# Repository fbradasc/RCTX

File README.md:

# RCTX - Multi-band R/C System

**Multi-band** because it's designed to work in the following **R/C** frequencies bands:

| Frequency | MHz/GHz | Supported               |
| :-------: | :-----: | :---------------------: |
| 13        |     MHz |                       y |
| 27        |     MHz |                       y |
| 30        |     MHz |                       y |
| 35        |     MHz |                       y |
| 40        |     MHz |                       y |
| 50-55     |     MHz |                       y |
| 70-75     |     MHz |                       y |
| 433       |     MHz |                       y |
| 440       |     MHz |                       y |
| 460       |     MHz |                       y |
| 866       |     MHz | with an external module |
| 900       |     MHz | with an external module |
| 2.4       |     GHz |                       y |

**System** because it's composed by two components:
- the **Encoder** (the remote command)
- the **Decoder** (the receiver)

## Common hardware description
Both components are designed around the Silicon Labs' **EFR32MG12** (_Multi-Protocol Wireless SoC_).

The **EFR32MG12** is equipped with both a _2.4 GHz_ transceiver and a _Sub-GHz_ transceiver tunable as low as _110 MHz_.

To go as low as 13 MHz the Sub-GHz transceiver is configured to work in the _110-350 MHz_ wideband and coupled with the Mini Cicruits' **ADE-1+** (_bidirectional double balanched diode mixer_) with a _LO_ frequency of _110 MHz_, as for the following frequency conversion scheme:
```
 10- 80 -(+110)-> 120-190 band pass
430-460 -(-110)-> 320-350 band pass

    10       80           430     460
     +--...--+             +--...--+
    /         \           /         \        [ Antennas ]
   /           \         /           \
--+             +--...--+             +--

                    ^
                    |
                    v
             110 ->(X)                       [ ADE-1+ ]
                    ^
                    |
                    v
    120     190           320     350
     +--...--+             +--...--+
    /         \           /         \        [ EFR32MG12 Sub-GHz transceiver ]
   /           \         /           \
--+             +--...--+             +--
```

#### Half and full duplex modes
Each **EFR32MG12** transceiver works in ***half duplex*** mode but using both at the same time a ***full duplex*** link between the **Encoder** and the **Decoder** can be established.

For example, the **Encoder** transmits the commands to the **Decoder** via the *Sub-GHz* channel and at the same time the **Decoder** transmits the telemetry to the **Encoder** on the *2.4 GHz* channel:
| Data | direction | Channel |
| :--: | :--: | :--: |
| _Commands_ | Encoder **-->** Decoder | _Sub-GHz_ |
| _Telemetry_ | Encoder **<--** Decoder | _2.4 GHz_ |

#### Utilities

Both components are designed to have the following utilities:
| connector | functionality |
| :-- | :-- |
| micro USB | logs and/or control from the PC |
| SD card | firmware upgrade, logs, configurations and telemetry storage |
| buzzer | acoustic feedback |
| Nokia 5110 display | GUI and data visualization |
| serial-interfaced LED driver (MAX6969 or MAX6971) | optical feedback for digital controls |

These utilities are built around the _Silicon Labs'_ **EFM32HG310** microcontroller which acts as an UART bridge to the SD card, Nokia 5110 display, LEDs and buzzer from the **EFR32MG12** point of view and as a CMSIS-DAP, TTY and MSD (SD Card) USB adapter from the PC point of view.
```
[EFR32MG12] <--(SPI)--> [EFM32HG310] <--(USB)--> [PC]
                             ^
                             |
                           (SPI)
                             |
                             v
             ,----------+----+----+---------.
             ^          |         |         |
             |          |         |         |
             v          v         v         v
         [SD Card]  [BUZZER]  [display]  [LEDs]
```

## Encoder

The **Encoder**'s role is to transform the status of the following controls, switches and buttons into commands to be trasmitted to a **Decoder** or R/C receiver:

| Control               | Count | Type    | Note                   |
| :-------------------- | :---: | :------ | :--------------------- |
| Lever sticks          |     4 | analog  |                        |
| Rotary controls       |    12 | analog  |                        |
| On/Mom/Off Switches   |    32 | analog  | converted from digital |
| Push buttons          |     8 | analog  | converted from digital |
| Push buttons          |     2 | digital |                        |

The commands are then incapsulated in a *protocol* and sent via a transmission channel to:

| Destination               | Channel            |
| :------------------------ | :----------------: |
| a **Decoder**             | Radio or ***TBD*** cable |
| a generic R/C receiver    | Radio              |
| another **Encoder**       | DSC cable          |
| a cable controlled device | I2C or UART cable  |

### ***Encoder*** configuration controls

The **Encoder**'s behaviour is controlled by a couple of DP3T (dual pole 3 pos) slide switches and 3 HEX selectors.

#### ***Encoder***'s output selection DP3T slide switch

This slide switch is used to select where the **Encoder**'s commands are sent:

| slide pos | on DSC cable | via radio | on serial cable |
| :-------: | :----------: | :-------: | :-------------: |
| side 1    | X            |           |                 |
| center    |              |           | X               |
| side 2    |              | X         |                 |

#### Configurable DP3T slide switch - **TBD**

This slide switch behaviour can be configured by the user - **TBD**

#### ***RF BAND SEL*** HEX selector

This HEX selector is used to set the RF band on which the **Encoder** can be tuned for commands transmission and telemetry reception:

| HEX pos | RF band       | MHz | GHz | Sub-GHz transceiver | GHz transceiver |
| :-----: | :------------ | :-: | :-: | :-----------------: | :-------------: |
|    0    | 13.560        |  X  |     |   ON: half-duplex   |       (1)       |
|    1    | 26.815-27.995 |  X  |     |   ON: half duplex   |       (1)       |
|    2    | 29.720-30.350 |  X  |     |   ON: half duplex   |       (1)       |
|    3    | 34.945-36.600 |  X  |     |   ON: half duplex   |       (1)       |
|    4    | 40.510-41.200 |  X  |     |   ON: half duplex   |       (1)       |
|    5    | 49.830-50.980 |  X  |     |   ON: half duplex   |       (1)       |
|    6    | 53.100-54.550 |  X  |     |   ON: half duplex   |       (1)       |
|    7    | 70.140        |  X  |     |   ON: half duplex   |       (1)       |
|    8    | 72.010        |  X  |     |   ON: half duplex   |       (1)       |
|    9    | 75.410        |  X  |     |   ON: half duplex   |       (1)       |
|    A    | 433.250       |  X  |     |   ON: half duplex   |       (1)       |
|    B    | 434.025       |  X  |     |   ON: half duplex   |       (1)       |
|    C    | 439.700       |  X  |     |   ON: half duplex   |       (1)       |
|    D    | 458.500       |  X  |     |   ON: half duplex   |       (1)       |
|    E    | 459.500       |  X  |     |   ON: half duplex   |       (1)       |
|    F    | 2.4           |     |  X  |        OFF          | ON: half duplex |

(1): Can be configured to be **ON: half duplex** for **Decoder**s which send on the 2.4 GHz band the *telemetry* back to the **Encoder**

#### ***RX ID*** and ***RX SUB ID*** HEX selectors

The **Encoder**'s custom trasmission protocol is composed by commands packets which can be addressed to up to 256 recipients.

This means that on a given frequncy, and bound to the **Encoder** at the same time, can be tuned:

- Up to 16 (**RX ID**) **Decoder**s each one with up to 15 (**RX SUB ID**) aditional addressable sub modules
- Up to 256 (**RX ID**:**RX SUB ID**) **Decoder**s with no sub modules

#### Robbe/Futaba F14 radio with RCTX mods

|#|Description|Reference on the picture|
|:-:|:-|:-|
|10|micro push buttons|**1** to **8**, **PL** and **PR**|
|16|*Mom-OFF-Mom* switches|**M1** to **M16**|
|2|*DP3T* slide switches|**SL** and **SR**|
|2|R/C sticks|**LEFT STICK** and **RIGHT STICK**|
|12|rotary controls|**R1** to **R12**|
|1|amperometer|**battery level indicator**|
|36|LEDs|on the side and above the **battery level indicator**|
|1|display|**Nokia 5110 display**|
|1|USB connector|**mini USB**|
|1|DB9 connector|flash programming and debug connections|
|1|DB15 connector|on the bottom side of the radio, expansion port with **UART**, **I2C**, **DSC** and tranceivers' mode connections|
|1|micro SD slot|**Kingston micro SD Card adapter**|
|3|hexadecimal encoders|**RX *ID***, **RX *SUB ID*** and ***RF* BAND SEL**|
|1|power switch|**ON/OFF**|

## Decoder

The **Decoder**'s main role is to produce a stream of signals on the *CRSF (Crossfire) bus* to control the actuators attached to such communication bus.

To achieve this task the **Decoder** merges the data coming from the sensors attached to its I2C bus with the commands trasmitted by the **Encoder** (either via radio or via ***TBD*** cable.

The **Decoder**, if configured, then compresses the sensors data and the signals produced in a format suitable to be stored on the SD card and to be transmitted back to the **Encoder** as ***telemetry*** data.

### Decoder configuration controls

The **Decoder**'s behaviour is controlled by 3 HEX selectors and a DIP switch.

#### ***RX ID*** and ***RX SUB ID*** HEX selectors

These HEX selectors are used to set the **Decoder**'s address.
Only the commands addressed to its own address (**RX ID** and **RX SUB ID** positions) are processed.

#### ***RF BAND SEL*** HEX selector

This HEX selector is used to set the RF band on which the **Decoder** can be tuned for commands reception and telemetry transmission:

| HEX pos | RF band       | MHz | GHz | Sub-GHz transceiver | GHz transceiver |
| :-----: | :------------ | :-: | :-: | :-----------------: | :-------------: |
|    0    | 13.560        |  X  |     |   ON: half-duplex   |       (1)       |
|    1    | 26.815-27.995 |  X  |     |   ON: half duplex   |       (1)       |
|    2    | 29.720-30.350 |  X  |     |   ON: half duplex   |       (1)       |
|    3    | 34.945-36.600 |  X  |     |   ON: half duplex   |       (1)       |
|    4    | 40.510-41.200 |  X  |     |   ON: half duplex   |       (1)       |
|    5    | 49.830-50.980 |  X  |     |   ON: half duplex   |       (1)       |
|    6    | 53.100-54.550 |  X  |     |   ON: half duplex   |       (1)       |
|    7    | 70.140        |  X  |     |   ON: half duplex   |       (1)       |
|    8    | 72.010        |  X  |     |   ON: half duplex   |       (1)       |
|    9    | 75.410        |  X  |     |   ON: half duplex   |       (1)       |
|    A    | 433.250       |  X  |     |   ON: half duplex   |       (1)       |
|    B    | 434.025       |  X  |     |   ON: half duplex   |       (1)       |
|    C    | 439.700       |  X  |     |   ON: half duplex   |       (1)       |
|    D    | 458.500       |  X  |     |   ON: half duplex   |       (1)       |
|    E    | 459.500       |  X  |     |   ON: half duplex   |       (1)       |
|    F    | 2.4           |     |  X  |        OFF          | ON: half duplex |

(1): Can be configured to be **ON: half duplex** for **Decoder**s which send on the 2.4 GHz band the *telemetry* back to the **Encoder**.

#### ***RX RADIO EN*** DIP switch

This DIP switch is used to set the ***Decoder***'s source for incoming commands:

- **RX RADIO EN** in position ***1*** *(open)*

    The **Decoder** listens for commands signal on the **DSC_BUS** bus:
    - Turns OFF the radio transceiver.
    - Commands signal can only be received from the ***DSC_BUS***.
    - Telemetry data can only be send to the ***DSC_BUS***.

- **RX RADIO EN** in position ***2*** *(closed)*

    The **Decoder** listens for commands coming from the radio:
    - Turns ON the radio tranceivers.
    - Commands signal can only be received from the radio transceiver.
    - Commands signal received from the radio transceiver is mirrored, as is, over the ***DSC_BUS***.
    - Telemetry data can only be send to the radio transceiver.
    - Telemetry data received from the ***DSC_BUS*** is fused with the local telemetry data before it's sent to the radio transceiver.

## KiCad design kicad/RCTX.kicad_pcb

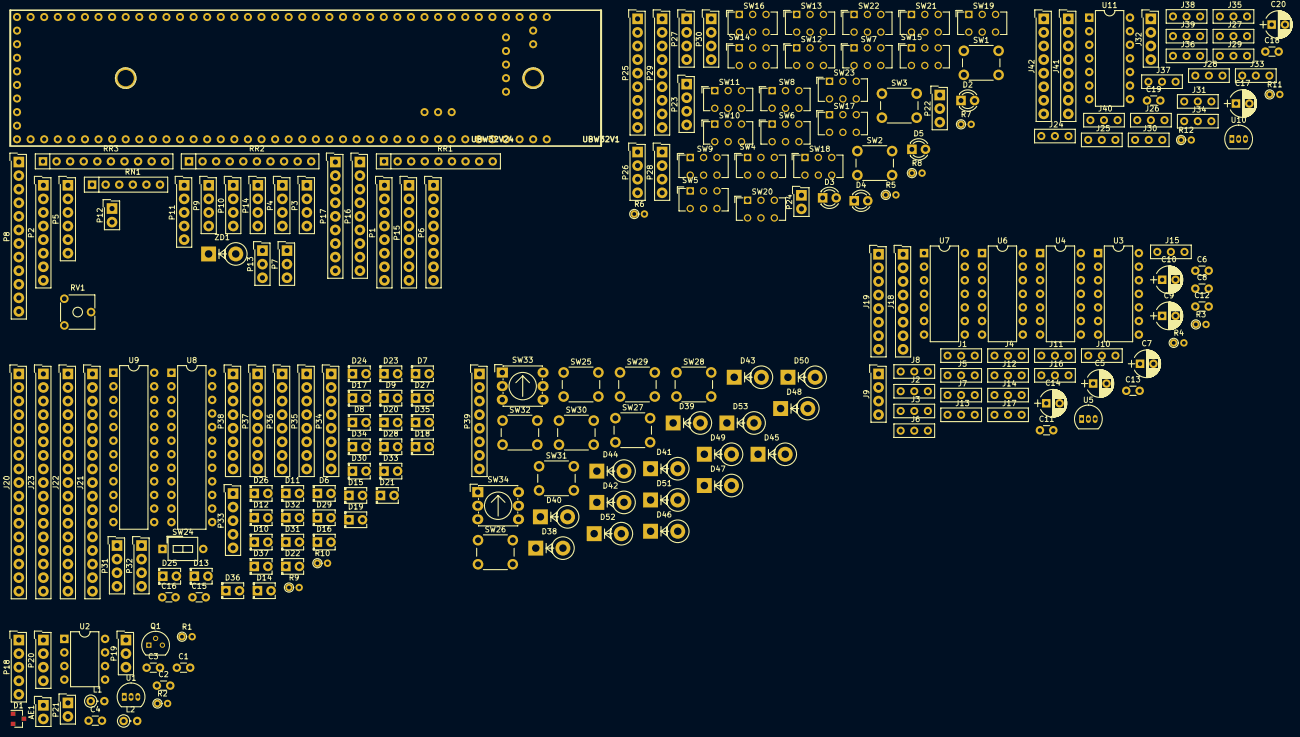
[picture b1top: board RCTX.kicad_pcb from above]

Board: 2 copper layers, 222 parts (0 on the bottom side), 305 nets, no tracks yet.

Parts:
AE1: Antenna_Shield; SL-102-X-XX_1x02
C1, C12, C18: 100nF; C_Disc_D3.0mm_W1.6mm_P2.50mm
C2, C3: 10nF; C_Disc_D3.0mm_W1.6mm_P2.50mm
C4: 1nF; C_Disc_D3.0mm_W1.6mm_P2.50mm
C5, C9, C10, C14: 100uF; CP_Radial_D5.0mm_P2.50mm
C6, C8, C11, C13: 1uF; C_Disc_D3.0mm_W1.6mm_P2.50mm
C7, C17: 1uF; CP_Radial_D5.0mm_P2.50mm
C15, C16: 0.1uF; C_Disc_D3.0mm_W1.6mm_P2.50mm
C19: C; C_Disc_D3.0mm_W1.6mm_P2.50mm
C20: CP; CP_Radial_D5.0mm_P2.50mm
D1: BAV99; SOT-23
D2: RED; LED_D3.0mm
D3: WHITE; LED_D3.0mm
D4: GREEN; LED_D3.0mm
D5: BLUE; LED_D3.0mm
D6, D7, D8, D9, D10, D11, D12, D13, D14, D15, D16, D17, D18, D19, D20, D21, D22, D23, D24, D25, D26, D27, D28, D29, D30, D31, D32, D33, D34, D35, D36, D37: LED; LED_D2.0mm_W4.0mm_H2.8mm_FlatTop
D38, D39, D40, D41, D42, D43, D44, D45, D46, D47, D48, D49, D50, D51, D52, D53: 1N4148; D_5W_P5.08mm_Vertical_KathodeUp
J1, J24: ROTARY_4; SRV_1
J2, J25: ROTARY_5; SRV_1
J3, J26: ROTARY_3; SRV_1
J4, J27: ROTARY_6; SRV_1
J5, J28: ROTARY_2; SRV_1
J6, J29: ROTARY_7; SRV_1
J7, J30: ROTARY_1; SRV_1
J8, J31: ROTARY_8; SRV_1
J9, J32: PWR_BUS; SL-104-X-XX_1x04
J10, J33: H_RIGHT_JOYSTIC; SRV_1
J11, J34: ROTARY_9; SRV_1
J12, J35: V_RIGHT_JOYSTIC; SRV_1
J13, J36: ROTARY_10; SRV_1
J14, J37: H_LEFT_JOYSTIC; SRV_1
J15, J38: ROTARY_11; SRV_1
J16, J39: V_LEFT_JOYSTIC; SRV_1
J17, J40: ROTARY_12; SRV_1
J18, J41: MULTI_PROP_1; SL-108-X-XX_1x08
J19, J42: MULTI_PROP_2; SL-108-X-XX_1x08
J20, J21, J22, J23: Conn_01x17; SL-117-X-XX_1x17
L1: Pickup coil; L_Axial_L5.3mm_D2.2mm_P2.54mm_Vertical_Vishay_IM-1
L2: 10uH; L_Axial_L5.3mm_D2.2mm_P2.54mm_Vertical_Vishay_IM-1
P1: MULTI_PROP_1; SL-108-X-XX_1x08
P2: MULTI_PROP_2; SL-108-X-XX_1x08
P3: SD_CARD; SL-104-X-XX_1x04
P4, P32: LEDs; SL-104-X-XX_1x04
P5: DISPLAY; SL-106-X-XX_1x06
P6: EJTAG + IO_PORT; SL-108-X-XX_1x08
P7, P19: TX_MOD; SL-103-X-XX_1x03
P8: AUX_DB15_PORT; SL-112-X-XX_1x12
P9, P20, P23, P26, P28, P30, P31: PWR_BUS; SL-104-X-XX_1x04
P10: POWER_IN; SL-104-X-XX_1x04
P11: USB; SL-105-X-XX_1x05
P12: BUZZ; SL-102-X-XX_1x02
P13, P22: SW; SL-103-X-XX_1x03
P14, P27: LEDS; SL-104-X-XX_1x04
P15: KEYPAD; SL-108-X-XX_1x08
P16, P25: MULTI_DIGITAL_1; SL-109-X-XX_1x09
P17, P29: MULTI_DIGITAL_2; SL-109-X-XX_1x09
P18: RF MODULE; SL-105-X-XX_1x05
P21, P24: TX_VCC; SL-102-X-XX_1x02
P33: DISPLAY; SL-105-X-XX_1x05
P34, P35, P37, P38: CONN_8; SL-108-X-XX_1x08
P36: Nokia 5110 Display; SL-108-X-XX_1x08
P39: KEYBOARD; SL-108-X-XX_1x08
Q1: BC547; TO-92_Molded_Narrow
R1: 2k2; R_Axial_DIN0204_L3.6mm_D1.6mm_P1.90mm_Vertical
R2: 15k; R_Axial_DIN0204_L3.6mm_D1.6mm_P1.90mm_Vertical
R3, R11: 470; R_Axial_DIN0204_L3.6mm_D1.6mm_P1.90mm_Vertical
R4, R12: 150; R_Axial_DIN0204_L3.6mm_D1.6mm_P1.90mm_Vertical
R5, R6, R7, R8: 330; R_Axial_DIN0204_L3.6mm_D1.6mm_P1.90mm_Vertical
R9, R10: R; R_Axial_DIN0204_L3.6mm_D1.6mm_P1.90mm_Vertical
RN1: 15k; R_Array_SIP6
RR1: 15k; R_Array_SIP9
RR2, RR3: 15K; R_Array_SIP10
RV1: POT; Potentiometer_Trimmer_ACP_CA6v_Horizontal
SW1: Reset; SW_PUSH_6mm_h5mm
SW2: Program; SW_PUSH_6mm_h5mm
SW3: User; SW_PUSH_6mm_h5mm
SW4: RF_SWITCH_3P2V; SW_CuK_JS202011AQN_DPDT_Angled
SW5: LEFT_3P2V; SW_CuK_JS202011AQN_DPDT_Angled
SW6, SW7, SW8, SW9, SW10, SW11, SW12, SW13: LEFT_3P1V; SW_CuK_JS202011CQN_DPDT_Straight
SW14: RIGHT_3P2V_B; SW_CuK_JS202011AQN_DPDT_Angled
SW15: RIGHT_3P2V_A; SW_CuK_JS202011AQN_DPDT_Angled
SW16, SW17, SW18, SW19, SW20, SW21, SW22, SW23: RIGHT_3P1V; SW_CuK_JS202011CQN_DPDT_Straight
SW24: LED_SWITCH; SW_DIP_x1_W7.62mm_Slide_LowProfile
SW25, SW26, SW27, SW28, SW29, SW30, SW31, SW32: SPST; SW_PUSH_6mm_h5mm
SW33, SW34: CODING_SWITCH; Nidec_Copal_SH-7010C
U1: LM78L05_TO92; TO-92_Inline_Narrow_Oval
U2: MB504L; DIP-8_W7.62mm
U3, U4, U6, U7, U11: LM324; DIP-14_W7.62mm
U5, U10: LM117_TO3; TO-92_Inline_Narrow_Oval
U8, U9: MAX6969; DIP-24_W7.62mm
UBW32V1: UBW32V24; UBW32_V24
ZD1: ZENER; D_5W_P5.08mm_Vertical_KathodeUp

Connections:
+3V3: AE1.2, C1.1, C2.2, C3.2, C5.2, C6.1, C7.2, C8.1, C9.2, C10.2, C11.1, C12.1, C12.2, C13.1, C14.2, C17.2, C18.1, C18.2, C19.1, C20.2, J1.1, J2.1, J3.1, J4.1, J5.1, J6.1, J7.1, J8.1, J9.1, J9.3, J10.1, J10.3, J11.1, J12.1, J12.3, J13.1, J14.1, J14.3, J15.1, J16.1, J16.3, J17.1, J24.1, J25.1, J26.1, J27.1, J28.1, J29.1, J30.1, J31.1, J32.1, J32.3, J33.1, J33.3, J34.1, J35.1, J35.3, J36.1, J37.1, J37.3, J38.1, J39.1, J39.3, J40.1, L2.1, P9.1, P9.3, P18.2, P20.1, P20.3, P23.3, P26.1, P26.3, P28.1, P30.1, P30.3, P31.1, P31.3, P34.1, P34.7, P35.1, P35.7, P36.1, P36.2, Q1.3, R1.2, R4.1, R5.2, R6.2, R7.2, R8.2, R12.1, RN1.1, RR1.1, SW1.1, SW2.1, SW3.1, SW5.1, SW5.4, SW6.1, SW6.3, SW7.1, SW7.3, SW8.1, SW8.3, SW9.1, SW9.3, SW10.1, SW10.3, SW11.1, SW11.3, SW12.1, SW12.3, SW13.1, SW13.3, SW15.1, SW15.4, SW16.1, SW16.3, SW17.1, SW17.3, SW18.1, SW18.3, SW19.1, SW19.3, SW20.1, SW20.3, SW21.1, SW21.3, SW22.1, SW22.3, SW23.1, SW23.3, SW24.1, U1.2, U2.4, U3.11, U4.11, U5.2, U6.11, U7.11, U10.2, U11.11, UBW32V1.1, UBW32V1.3, UBW32V1.86
+5V: C1.2, C2.1, C5.1, C6.2, C8.2, C9.1, C10.1, C11.2, C13.2, C14.1, C19.2, C20.1, J9.2, J32.2, P9.2, U1.1, U2.2, U2.3, U2.6, U3.4, U4.4, U6.4, U7.4, U11.4, UBW32V1.2
unnamed: AE1.1, P18.1
unnamed: C3.1, P18.4, P21.2, U1.3
unnamed: C4.1, Q1.2
unnamed: C4.2, R1.1
unnamed: C7.1, J1.3, J2.3, J3.3, J4.3, J5.3, J6.3, J7.3, J8.3, J11.3, J13.3, J15.3, J17.3, R3.1, U5.3
unnamed: C15.1, P37.1, R9.1, U8.1
unnamed: C15.2, P37.7, U8.24
unnamed: C16.1, P38.1, R10.1, U9.1
unnamed: C16.2, P38.7, U9.24
unnamed: C17.1, J24.3, J25.3, J26.3, J27.3, J28.3, J29.3, J30.3, J31.3, J34.3, J36.3, J38.3, J40.3, R11.1, U10.3
unnamed: D1.1, D1.2, L1.1, U2.1
unnamed: D1.3, L1.2, U2.8
unnamed: D2.1, R5.1
unnamed: D2.2, P27.1
unnamed: D3.1, R6.1
unnamed: D3.2, P27.2
unnamed: D4.1, R7.1
unnamed: D4.2, P27.3
unnamed: D5.1, R8.1
unnamed: D5.2, P27.4
unnamed: D6.2, J22.2
unnamed: D7.2, J23.2
unnamed: D8.2, J22.3
unnamed: D9.2, J23.3
unnamed: D6.1, D8.1, D10.1, D12.1, D14.1, D16.1, D18.1, D20.1, D22.1, D24.1, D26.1, D28.1, D30.1, D32.1, D34.1, D36.1, J22.1
unnamed: D10.2, J22.4
unnamed: D7.1, D9.1, D11.1, D13.1, D15.1, D17.1, D19.1, D21.1, D23.1, D25.1, D27.1, D29.1, D31.1, D33.1, D35.1, D37.1, J23.1
unnamed: D11.2, J23.4
unnamed: D12.2, J22.5
unnamed: D13.2, J23.5
unnamed: D14.2, J22.6
unnamed: D15.2, J23.6
unnamed: D16.2, J22.7
unnamed: D17.2, J23.7
unnamed: D18.2, J22.8
unnamed: D19.2, J23.8
unnamed: D20.2, J22.9
unnamed: D21.2, J23.9
unnamed: D22.2, J22.10
unnamed: D23.2, J23.10
unnamed: D24.2, J22.11
unnamed: D25.2, J23.11
unnamed: D26.2, J22.12
unnamed: D27.2, J23.12
unnamed: D28.2, J22.13
unnamed: D29.2, J23.13
unnamed: D30.2, J22.14
unnamed: D31.2, J23.14
unnamed: D32.2, J22.15
unnamed: D33.2, J23.15
unnamed: D34.2, J22.16
unnamed: D35.2, J23.16
unnamed: D36.2, J22.17
unnamed: D37.2, J23.17
unnamed: D38.1, D42.1, D46.1, D50.1, P39.5
unnamed: D38.2, SW25.1
unnamed: D39.1, D43.1, D47.1, D51.1, P39.6
unnamed: D39.2, SW26.1
unnamed: D40.1, D44.1, D48.1, D52.1, P39.7
unnamed: D40.2, SW27.1
unnamed: D41.1, D45.1, D49.1, D53.1, P39.8
unnamed: D41.2, SW28.1
unnamed: D42.2, SW29.1
unnamed: D43.2, SW30.1
unnamed: D44.2, SW31.1
unnamed: D45.2, SW32.1
unnamed: D47.2, SW33.4
unnamed: D49.2, SW33.2
unnamed: D51.2, SW34.4
unnamed: D53.2, SW34.2
unnamed: J1.2, U3.3
unnamed: J2.2, U3.5
unnamed: J3.2, U3.10
unnamed: J4.2, U3.12
unnamed: J5.2, U4.3
unnamed: J6.2, U4.5
unnamed: J7.2, U4.10
unnamed: J8.2, U4.12
unnamed: J10.2, U6.3
unnamed: J11.2, U6.5
unnamed: J12.2, U6.10
unnamed: J13.2, U6.12
unnamed: J14.2, U7.3
unnamed: J15.2, U7.5
unnamed: J16.2, U7.10
unnamed: J17.2, U7.12
unnamed: J18.1, U7.8, U7.9
unnamed: J18.2, U7.1, U7.2
unnamed: J18.3, U6.8, U6.9
unnamed: J18.4, U6.1, U6.2
unnamed: J18.5, U4.8, U4.9
unnamed: J18.6, U4.1, U4.2
unnamed: J18.7, U3.8, U3.9
unnamed: J18.8, U3.1, U3.2
unnamed: J19.1, U3.6, U3.7
unnamed: J19.2, U3.13, U3.14
unnamed: J19.3, U4.6, U4.7
unnamed: J19.4, U4.13, U4.14
unnamed: J19.5, U6.6, U6.7
unnamed: J19.6, U6.13, U6.14
unnamed: J19.7, U7.6, U7.7
unnamed: J19.8, U7.13, U7.14
unnamed: J20.1, P37.8
unnamed: J20.2, U8.5
unnamed: J20.3, U8.6
unnamed: J20.4, U8.7
unnamed: J20.5, U8.8
unnamed: J20.6, U8.9
unnamed: J20.7, U8.10
unnamed: J20.8, U8.11
unnamed: J20.9, U8.12
unnamed: J20.10, U8.13
unnamed: J20.11, U8.14
unnamed: J20.12, U8.15
unnamed: J20.13, U8.16
unnamed: J20.14, U8.17
unnamed: J20.15, U8.18
unnamed: J20.16, U8.19
unnamed: J20.17, U8.20
unnamed: J21.1, P38.8
unnamed: J21.2, U9.5
unnamed: J21.3, U9.6
unnamed: J21.4, U9.7
unnamed: J21.5, U9.8
unnamed: J21.6, U9.9
unnamed: J21.7, U9.10
unnamed: J21.8, U9.11
unnamed: J21.9, U9.12
unnamed: J21.10, U9.13
unnamed: J21.11, U9.14
unnamed: J21.12, U9.15
unnamed: J21.13, U9.16
unnamed: J21.14, U9.17
unnamed: J21.15, U9.18
unnamed: J21.16, U9.19
unnamed: J21.17, U9.20
unnamed: J24.2, J41.8
unnamed: J25.2, J42.1
unnamed: J26.2, J41.7
unnamed: J27.2, J42.2
unnamed: J28.2, J41.6
unnamed: J29.2, J42.3
unnamed: J30.2, J41.5
unnamed: J31.2, J42.4
unnamed: J33.2, U11.3
unnamed: J34.2, J42.5
unnamed: J35.2, U11.5
unnamed: J36.2, J42.6
unnamed: J37.2, U11.10
unnamed: J38.2, J42.7
unnamed: J39.2, U11.12
unnamed: J40.2, J42.8
unnamed: J41.1, U11.13, U11.14
unnamed: J41.2, U11.8, U11.9
unnamed: J41.3, U11.6, U11.7
unnamed: J41.4, U11.1, U11.2
unnamed: L2.2, R2.1
unnamed: P1.1, UBW32V1.45
unnamed: P1.2, UBW32V1.44
unnamed: P1.3, UBW32V1.43
unnamed: P1.4, UBW32V1.42
unnamed: P1.5, UBW32V1.41
unnamed: P1.6, UBW32V1.31
unnamed: P1.7, UBW32V1.30
unnamed: P1.8, UBW32V1.29
unnamed: P2.1, UBW32V1.26
unnamed: P2.2, UBW32V1.25
unnamed: P2.3, UBW32V1.24
unnamed: P2.4, UBW32V1.23
unnamed: P2.5, UBW32V1.19
unnamed: P2.6, UBW32V1.18
unnamed: P2.7, UBW32V1.17
unnamed: P2.8, UBW32V1.16
unnamed: P3.1, P5.5, UBW32V1.39
unnamed: P3.2, P4.2, P5.4, UBW32V1.37
unnamed: P3.3, P5.3, UBW32V1.38
unnamed: P3.4, UBW32V1.33
unnamed: P4.1, UBW32V1.40
unnamed: P4.3, UBW32V1.32
unnamed: P4.4, UBW32V1.78
unnamed: P5.1, UBW32V1.28
unnamed: P5.2, UBW32V1.27
unnamed: P6.1, UBW32V1.36
unnamed: P6.2, UBW32V1.34
unnamed: P6.3, UBW32V1.22
unnamed: P6.4, UBW32V1.7
unnamed: P6.5, UBW32V1.6
unnamed: P6.6, P8.1, RN1.5, UBW32V1.9
unnamed: P6.7, P7.3, P8.2, RN1.4, UBW32V1.8
unnamed: P6.8, P7.2, RN1.6, UBW32V1.35
unnamed: P7.1, UBW32V1.49, UBW32V1.79
unnamed: P8.3, UBW32V1.21
unnamed: P8.4, UBW32V1.20
unnamed: P8.5, UBW32V1.15
unnamed: P8.6, UBW32V1.14
unnamed: P8.7, UBW32V1.13
unnamed: P8.8, UBW32V1.12
unnamed: P8.9, UBW32V1.11
unnamed: P8.10, UBW32V1.10
unnamed: P8.11, RN1.3, UBW32V1.5
unnamed: P8.12, RN1.2, UBW32V1.4
unnamed: P9.4, P10.1, RV1.1, UBW32V1.90
unnamed: P10.2, P10.3, UBW32V1.89
unnamed: P10.4, ZD1.2
unnamed: P11.1, UBW32V1.91
unnamed: P11.2, UBW32V1.92
unnamed: P11.3, UBW32V1.93
unnamed: P11.4, UBW32V1.94
unnamed: P11.5, UBW32V1.95
unnamed: P12.1, UBW32V1.81
unnamed: P12.2, UBW32V1.46
unnamed: P13.1, UBW32V1.48
unnamed: P13.2, UBW32V1.52
unnamed: P13.3, UBW32V1.53
unnamed: P14.1, UBW32V1.57
unnamed: P14.2, UBW32V1.58
unnamed: P14.3, UBW32V1.62
unnamed: P14.4, UBW32V1.63
unnamed: P15.1, RR1.2, UBW32V1.50
unnamed: P15.2, RR1.3, UBW32V1.51
unnamed: P15.3, RR1.4, UBW32V1.54
unnamed: P15.4, RR1.5, UBW32V1.55
unnamed: P15.5, RR1.6, UBW32V1.56
unnamed: P15.6, RR1.7, UBW32V1.59
unnamed: P15.7, RR1.8, UBW32V1.60
unnamed: P15.8, RR1.9, UBW32V1.61
unnamed: P16.1, RR2.2, UBW32V1.64
unnamed: P16.2, RR2.3, UBW32V1.65
unnamed: P16.3, RR2.4, UBW32V1.66
unnamed: P16.4, RR2.5, UBW32V1.67
unnamed: P16.5, RR2.6, UBW32V1.68
unnamed: P16.6, RR2.7, UBW32V1.69
unnamed: P16.7, RR2.8, UBW32V1.70
unnamed: P16.8, RR2.9, UBW32V1.71
unnamed: P16.9, RR2.10, UBW32V1.72
unnamed: P17.1, RR3.2, UBW32V1.73
unnamed: P17.2, RR3.3, UBW32V1.74
unnamed: P17.3, RR3.4, UBW32V1.75
unnamed: P17.4, RR3.5, UBW32V1.76
unnamed: P17.5, RR3.6, UBW32V1.77
unnamed: P17.6, RR3.7, UBW32V1.80
unnamed: P17.7, RR3.8, UBW32V1.82
unnamed: P17.8, RR3.9, UBW32V1.83
unnamed: P17.9, RR3.10, UBW32V1.84
unnamed: P18.3, P19.2
unnamed: P18.5, P19.3
unnamed: P19.1, Q1.1, R2.2
unnamed: P20.4, P21.1
unnamed: P22.1, SW1.2
unnamed: P22.2, SW2.2
unnamed: P22.3, SW3.2
unnamed: P24.1, SW4.3
unnamed: P24.2, SW4.1
unnamed: P25.1, SW5.3
unnamed: P25.2, SW6.2
unnamed: P25.3, SW7.2
unnamed: P25.4, SW8.2
unnamed: P25.5, SW9.2
unnamed: P25.6, SW10.2
unnamed: P25.7, SW11.2
unnamed: P25.8, SW12.2
unnamed: P25.9, SW13.2
unnamed: P29.1, SW15.3
unnamed: P29.2, SW16.2
unnamed: P29.3, SW17.2
unnamed: P29.4, SW18.2
unnamed: P29.5, SW19.2
unnamed: P29.6, SW20.2
unnamed: P29.7, SW21.2
unnamed: P29.8, SW22.2
unnamed: P29.9, SW23.2
unnamed: P31.4, P34.8, P35.8
unnamed: P32.1, P34.6, P35.6
unnamed: P32.2, P34.5
unnamed: P32.3, P34.3, P35.3
unnamed: P32.4, P34.2, P35.2
unnamed: P33.1, P36.3
unnamed: P33.2, P36.4
unnamed: P33.3, P36.5
unnamed: P33.4, P36.6
unnamed: P33.5, P36.7
unnamed: P34.4, P35.5
unnamed: P36.8, SW24.2
unnamed: P37.2, U8.21
unnamed: P37.3, U8.4
unnamed: P37.4, U8.22
unnamed: P37.5, U8.2
unnamed: P37.6, U8.3
unnamed: P38.2, U9.21
unnamed: P38.3, U9.4
unnamed: P38.4, U9.22
unnamed: P38.5, U9.2
unnamed: P38.6, U9.3
unnamed: P39.1, SW34.1
unnamed: P39.2, SW33.1
unnamed: P39.3, SW29.2, SW30.2, SW31.2, SW32.2
unnamed: P39.4, SW25.2, SW26.2, SW27.2, SW28.2
unnamed: R3.2, R4.2, U5.1
unnamed: R9.2, U8.23
unnamed: R10.2, U9.23
unnamed: R11.2, R12.2, U10.1
unnamed: RR2.1, RR3.1, UBW32V1.85
unnamed: RV1.2, RV1.3, ZD1.1

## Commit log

2019-09-24 Adding new schematic for analog inputs board
2019-09-29 Adding kicad schematics
2019-10-01 Adding 5110 display
2019-10-10 Adding footprints
2020-08-04 renaming switches, buttons and trims
2020-08-05 Fixing keypad wiring
2020-10-31 Adding Onsemi AX5043 based transmitter section
2020-11-02 Adding list of frequencies used in radio controlled models
2020-11-05 Adding tranceiver
2020-11-07 AX5043 inductors values for RC frequencies
2020-11-08 Using extended frequency ranges
2020-12-13 Adding transceiver
2020-12-20 New rx-tx bidirectional amplifier
2020-12-31 Using ERF32FG12 SoC instead of PIC32MX
2021-01-01 Splitting leds in dispay schema
2021-01-10 Adding wideband (110-350 MHz) matching network
2021-01-29 Using Pic16(L)F1459 as USB->(UART/SWD/I2C) bridge
2021-02-07 Adding micro SD socket in RCRX board
2021-03-21 Replacing Si500/Si510 clock generator with i2c controlled Si514 model
2021-09-24 Replacing discrete components rf filters with Mini-Circuits single chip filters
2021-09-24 Ignoring TOKEN file
2021-09-25 Fixed pinout for Max2650
2021-10-07 Choosing filter for low frequences bands
2023-05-26 Refactoring SD card and LCD control
2023-05-27 Adding PIB USB BRIDGE UML state diagrams
2023-05-30 Adding PIB USB BRIDGE UML state diagrams - WIP
2023-06-04 Adding PIC docs
2023-06-05 Reset PIC by cutting off Vdd via a n/c SW instead of grounding the USB VBUS on Vpp via a n/o SW
2023-06-08 Changing the buzzer connector
2023-12-01 Using an930.1-efr32-series-1_2.4GHz-matching-guide.pdf values for 2.4 GHz matching network
2023-12-07 Using MAX6969/MAX6971 SPI LEDs driver
2023-12-07 Optimizing power lines
2023-12-12 Using SAMD11D14M instead of PIC16F1459 for USB bridge
2023-12-13 Using SAMD11D14M instead of PIC16F1459 for USB bridge - updating schematics
2023-12-15 Driving the EFR32 reset with the SAMD11 reset pin as GPIO to have an additional GPIO for the SPI {EFR32<->SAMD11} CLK
2023-12-15 Adding micro SD card slot in RX circuit
2023-12-22 Using EFM32HG310-QFN32 instead of SAMD11D14M for USB bridge - updating schematics
2023-12-31 Using 8x4 sqaure symbol for EFM32HG310-QFN32
2024-01-01 Cleanup
2024-01-08 Updated README.txt for EFM32HG310 SPI extender / USB bridge
2024-01-10 Updated the README.md with the preliminary description of the project
2024-01-11 Added HEX rotary encoder and DIP switch for RX SUB ID selection in the receiver circuit. Updated README.md
2024-01-11 Updated README.md
    Fix new line in decoder address selection description
2024-01-12 Adding F14 radio with RCTX mods
2024-01-12 Update README.md
    Added description of the F14 mods for the RCTX transmitter
2024-01-19 Update README.md Updated the Decoder description
2024-01-19 Update README.md
    Fixed typo
